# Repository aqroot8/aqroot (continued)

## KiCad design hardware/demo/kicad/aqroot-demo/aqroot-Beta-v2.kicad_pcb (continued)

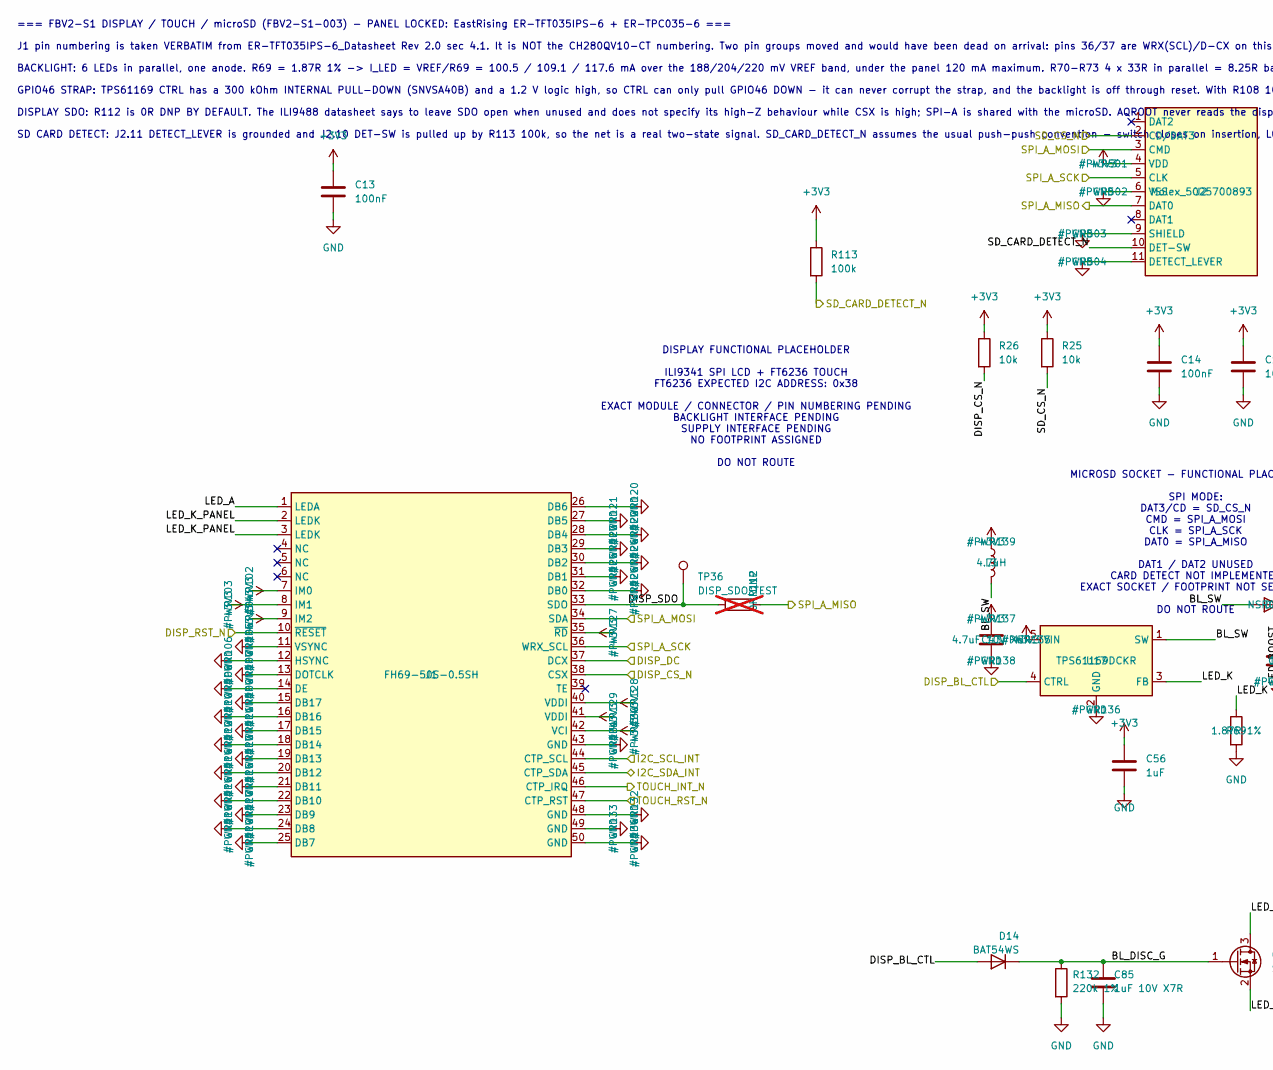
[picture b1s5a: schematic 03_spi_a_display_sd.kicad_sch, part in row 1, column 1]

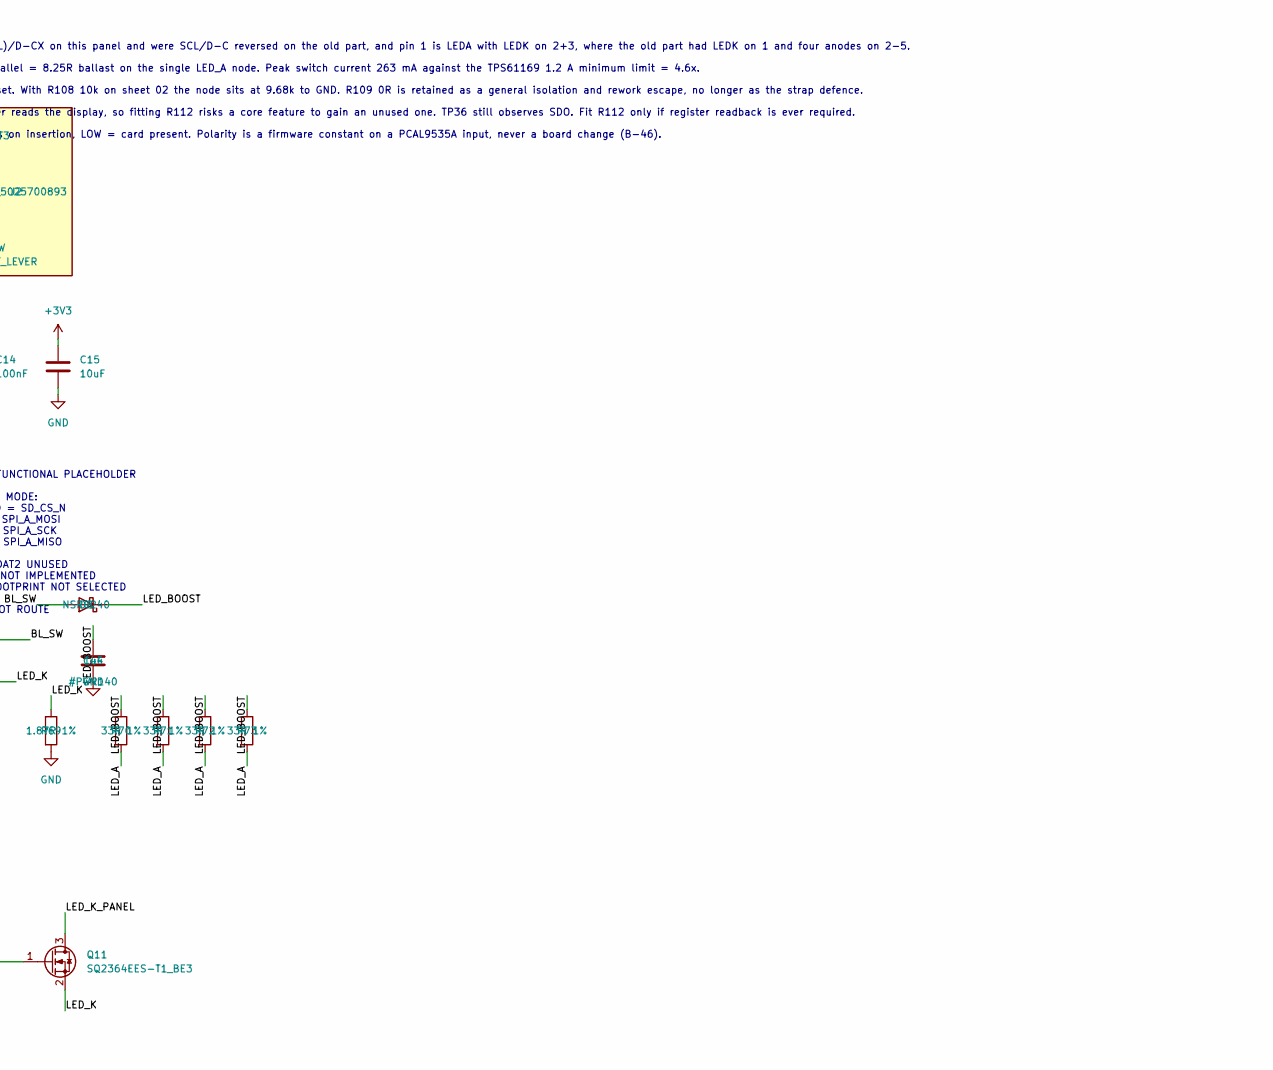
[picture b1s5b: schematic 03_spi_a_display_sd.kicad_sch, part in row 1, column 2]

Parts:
C13, C14: 100nF; C_0603_1608Metric; MPN CC0603KRX7R9BB104; LCSC C14663
C15: 10uF; C_0805_2012Metric; MPN GRM21BR61H106KE43L; LCSC C440198
C43: 4.7uF 10V X5R; C_0805_2012Metric; Voltage 16V; MPN CL21A475KAQNNNE; LCSC C1779
C44: 1uF; C_0805_2012Metric; Voltage 50V; MPN CL21B105KBFNNNE; LCSC C28323
C56: 1uF; C_0603_1608Metric; Voltage 16V; MPN CL10A105KB8NNNC; LCSC C15849
C85: 1uF 10V X7R; C_0603_1608Metric; MPN CC0603KRX7R8BB105; LCSC C106858
D8: NSR0240; D_SOD-323; MPN NSR0240HT1G; LCSC C152519
D14: BAT54WS; D_SOD-323; MPN BAT54WS-7-F; LCSC C124205
J1: FH69-50S-0.5SH; Hirose_FH69-50S-0.5SH; MPN FH69-50S-0.5SH; LCSC C25955556
J2: Molex_5025700893; MPN 5025700893; LCSC C429846
L3: 4.7uH; Coilcraft_XFL4020; MPN XFL4020-472MEC; LCSC C5156236
Q11: SQ2364EES-T1_BE3; SOT-23; MPN SQ2364EES-T1_BE3; LCSC C5758702
R25, R26: 10k; R_0603_1608Metric; MPN 0603WAF1002T5E; LCSC C25804
R69: 1.87R 1%; R_0603_1608Metric; Tolerance 1%; MPN 0603WAF187KT5E; LCSC C422967
R70, R71, R72, R73: 33R 1%; R_0603_1608Metric; Tolerance 1%; MPN 0603WAF330JT5E; LCSC C23140
R112: 0R DNP; R_0603_1608Metric; not fitted
R113: 100k; R_0603_1608Metric; MPN 0603WAF1003T5E; LCSC C25803
R132: 220k 1%; R_0603_1608Metric; MPN 0603WAF2203T5E; LCSC C22961
TP36: DISP_SDO_TEST; TestPoint_Pad_D1.0mm
U17: TPS61169DCKR; SOT-353_SC-70-5; MPN TPS61169DCKR; LCSC C71045

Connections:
+3V3: C13.1, C14.1, C15.1, C43.1, C56.1, J1.7 (IM0), J1.8 (IM1), J1.9 (IM2), J1.35 (~RD), J1.40 (VDDI), J1.41 (VDDI), J1.42 (VCI), J2.4 (VDD), L3.1, R25.1, R26.1, R113.1, U17.5 (VIN); also elsewhere on the board
/03_SPI_A_DISPLAY_SD/BL_DISC_G: C85.1, D14.1 (K), Q11.1 (G), R132.1
/03_SPI_A_DISPLAY_SD/BL_SW: D8.2 (A), L3.2, U17.1 (SW)
/03_SPI_A_DISPLAY_SD/DISP_SDO: J1.33 (SDO), R112.1, TP36.1
/03_SPI_A_DISPLAY_SD/LED_A: J1.1 (LEDA), R70.2, R71.2, R72.2, R73.2
/03_SPI_A_DISPLAY_SD/LED_BOOST: C44.1, D8.1 (K), R70.1, R71.1, R72.1, R73.1
/03_SPI_A_DISPLAY_SD/LED_K: Q11.2 (S), R69.1, U17.3 (FB)
/03_SPI_A_DISPLAY_SD/LED_K_PANEL: J1.2 (LEDK), J1.3 (LEDK), Q11.3 (D)
/DISP_BL_CTL: D14.2 (A), U17.4 (CTRL); also elsewhere on the board
/DISP_CS_N: J1.38 (CSX), R26.2; also elsewhere on the board
/DISP_DC: J1.37 (DCX); also elsewhere on the board
/DISP_RST_N: J1.10 (~RESET); also elsewhere on the board
/I2C_SCL_INT: J1.44 (CTP_SCL); also elsewhere on the board
/I2C_SDA_INT: J1.45 (CTP_SDA); also elsewhere on the board
/SD_CARD_DETECT_N: J2.10 (DET-SW), R113.2; also elsewhere on the board
/SD_CS_N: J2.2 (CD/DAT3), R25.2; also elsewhere on the board
/SPI_A_MISO: J2.7 (DAT0), R112.2; also elsewhere on the board
/SPI_A_MOSI: J1.34 (SDA), J2.3 (CMD); also elsewhere on the board
/SPI_A_SCK: J1.36 (WRX_SCL), J2.5 (CLK); also elsewhere on the board
/TOUCH_INT_N: J1.46 (CTP_IRQ); also elsewhere on the board
/TOUCH_RST_N: J1.47 (CTP_RST); also elsewhere on the board
GND: C13.2, C14.2, C15.2, C43.2, C44.2, C56.2, C85.2, J1.11 (VSYNC), J1.12 (HSYNC), J1.13 (DOTCLK), J1.14 (DE), J1.15 (DB17), J1.16 (DB16), J1.17 (DB15), J1.18 (DB14), J1.19 (DB13), J1.20 (DB12), J1.21 (DB11), J1.22 (DB10), J1.23 (DB9), J1.24 (DB8), J1.25 (DB7), J1.26 (DB6), J1.27 (DB5), J1.28 (DB4), J1.29 (DB3), J1.30 (DB2), J1.31 (DB1), J1.32 (DB0), J1.43 (GND), J1.48 (GND), J1.49 (GND), J1.50 (GND), J2.6 (VSS), J2.9 (SHIELD), J2.11 (DETECT_LEVER), R69.2, R132.2, U17.2 (GND); also elsewhere on the board

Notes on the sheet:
DISPLAY FUNCTIONAL PLACEHOLDER ILI9341 SPI LCD + FT6236 TOUCH FT6236 EXPECTED I2C ADDRESS: 0x38 EXACT MODULE / CONNECTOR / PIN NUMBERING PENDING BACKLIGHT INTERFACE PENDING SUPPLY INTERFACE PENDING NO FOOTPRINT ASSIGNED DO NOT ROUTE
MICROSD SOCKET - FUNCTIONAL PLACEHOLDER SPI MODE: DAT3/CD = SD_CS_N CMD = SPI_A_MOSI CLK = SPI_A_SCK DAT0 = SPI_A_MISO DAT1 / DAT2 UNUSED CARD DETECT NOT IMPLEMENTED EXACT SOCKET / FOOTPRINT NOT SELECTED DO NOT ROUTE
=== FBV2-S1 DISPLAY / TOUCH / microSD (FBV2-S1-003) - PANEL LOCKED: EastRising ER-TFT035IPS-6 + ER-TPC035-6 ===
J1 pin numbering is taken VERBATIM from ER-TFT035IPS-6_Datasheet Rev 2.0 sec 4.1. It is NOT the CH280QV10-CT numbering. Two pin groups moved and would have been dead on arrival: pins 36/37 are WRX(SCL)/D-CX on this panel and were SCL/D-C reversed on the old part, and pin 1 is LEDA with LEDK on 2+3,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
BACKLIGHT: 6 LEDs in parallel, one anode. R69 = 1.87R 1% -> I_LED = VREF/R69 = 100.5 / 109.1 / 117.6 mA over the 188/204/220 mV VREF band, under the panel 120 mA maximum. R70-R73 4 x 33R in parallel = 8.25R ballast on the single LED_A node. Peak switch current 263 mA against the TPS61169 1.2 A mini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
GPIO46 STRAP: TPS61169 CTRL has a 300 kOhm INTERNAL PULL-DOWN (SNVSA40B) and a 1.2 V logic high, so CTRL can only pull GPIO46 DOWN - it can never corrupt the strap, and the backlight is off through reset. With R108 10k on sheet 02 the node sits at 9.68k to GND. R109 0R is retained as a general isol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
DISPLAY SDO: R112 is 0R DNP BY DEFAULT. The ILI9488 datasheet says to leave SDO open when unused and does not specify its high-Z behaviour while CSX is high; SPI-A is shared with the microSD. AQROOT never reads the display, so fitting R112 risks a core feature to gain an unused one. TP36 still obse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
SD CARD DETECT: J2.11 DETECT_LEVER is grounded and J2.10 DET-SW is pulled up by R113 100k, so the net is a real two-state signal. SD_CARD_DETECT_N assumes the usual push-push convention - switch closes on insertion, LOW = card present. Polarity is a firmware constant on a PCAL9535A input, never a b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

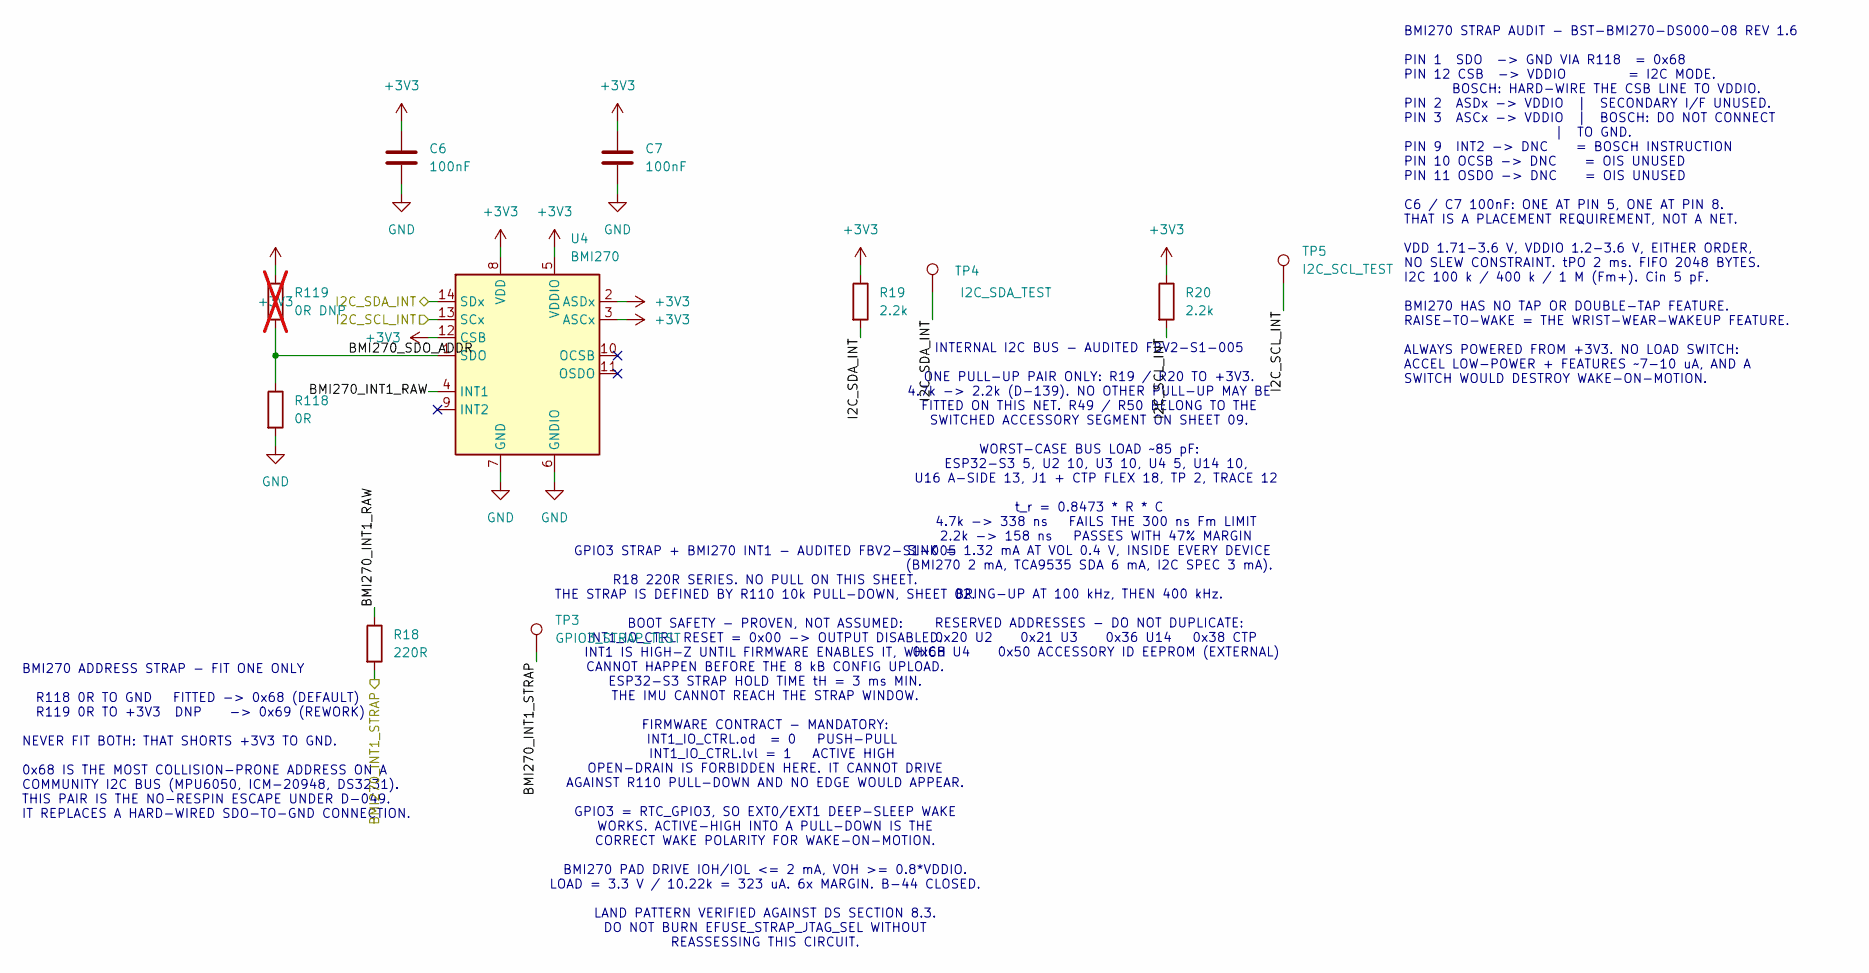
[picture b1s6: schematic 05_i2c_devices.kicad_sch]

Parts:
C6, C7: 100nF; C_0603_1608Metric; MPN CC0603KRX7R9BB104; LCSC C14663
R18: 220R; R_0603_1608Metric; MPN 0603WAF2200T5E; LCSC C22962
R19, R20: 2.2k; R_0603_1608Metric; MPN 0603WAF2201T5E; LCSC C4190
R118: 0R; R_0603_1608Metric; MPN 0603WAF0000T5E; LCSC C21189
R119: 0R DNP; R_0603_1608Metric; not fitted
TP3: GPIO3_STRAP_TEST; TestPoint_Pad_D1.0mm
TP4: I2C_SDA_TEST; TestPoint_Pad_D1.0mm
TP5: I2C_SCL_TEST; TestPoint_Pad_D1.0mm
U4: BMI270; Bosch_LGA-14_2.5x3.0mm_P0.5mm_BMI270; MPN BMI270; LCSC C2836813

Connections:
+3V3: C6.1, C7.1, R19.1, R20.1, R119.1, U4.2 (ASDx), U4.3 (ASCx), U4.5 (VDDIO), U4.8 (VDD), U4.12 (CSB); also elsewhere on the board
/05_I2C_DEVICES/BMI270_INT1_RAW: R18.1, U4.4 (INT1)
/05_I2C_DEVICES/BMI270_SDO_ADDR: R118.1, R119.2, U4.1 (SDO)
/BMI270_INT1_STRAP: R18.2, TP3.1; also elsewhere on the board
/I2C_SCL_INT: R20.2, TP5.1, U4.13 (SCx); also elsewhere on the board
/I2C_SDA_INT: R19.2, TP4.1, U4.14 (SDx); also elsewhere on the board
GND: C6.2, C7.2, R118.2, U4.6 (GNDIO), U4.7 (GND); also elsewhere on the board

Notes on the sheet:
GPIO3 STRAP + BMI270 INT1 - AUDITED FBV2-S1-005 R18 220R SERIES. NO PULL ON THIS SHEET. THE STRAP IS DEFINED BY R110 10k PULL-DOWN, SHEET 02. BOOT SAFETY - PROVEN, NOT ASSUMED: INT1_IO_CTRL RESET = 0x00 -> OUTPUT DISABLED. INT1 IS HIGH-Z UNTIL FIRMWARE ENABLES IT, WHICH CANNOT HAPPEN BEFORE THE 8 k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
INTERNAL I2C BUS - AUDITED FBV2-S1-005 ONE PULL-UP PAIR ONLY: R19 / R20 TO +3V3. 4.7k -> 2.2k (D-139). NO OTHER PULL-UP MAY BE FITTED ON THIS NET. R49 / R50 BELONG TO THE SWITCHED ACCESSORY SEGMENT ON SHEET 09. WORST-CASE BUS LOAD ~85 pF: ESP32-S3 5, U2 10, U3 10, U4 5, U14 10, U16 A-SIDE 13, J1 + 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
BMI270 ADDRESS STRAP - FIT ONE ONLY R118 0R TO GND FITTED -> 0x68 (DEFAULT) R119 0R TO +3V3 DNP -> 0x69 (REWORK) NEVER FIT BOTH: THAT SHORTS +3V3 TO GND. 0x68 IS THE MOST COLLISION-PRONE ADDRESS ON A COMMUNITY I2C BUS (MPU6050, ICM-20948, DS3231). THIS PAIR IS THE NO-RESPIN ESCAPE UNDER D-049. IT R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
BMI270 STRAP AUDIT - BST-BMI270-DS000-08 REV 1.6 PIN 1 SDO -> GND VIA R118 = 0x68 PIN 12 CSB -> VDDIO = I2C MODE. BOSCH: HARD-WIRE THE CSB LINE TO VDDIO. PIN 2 ASDx -> VDDIO | SECONDARY I/F UNUSED. PIN 3 ASCx -> VDDIO | BOSCH: DO NOT CONNECT | TO GND. PIN 9 INT2 -> DNC = BOSCH INSTRUCTION PIN 10 OC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

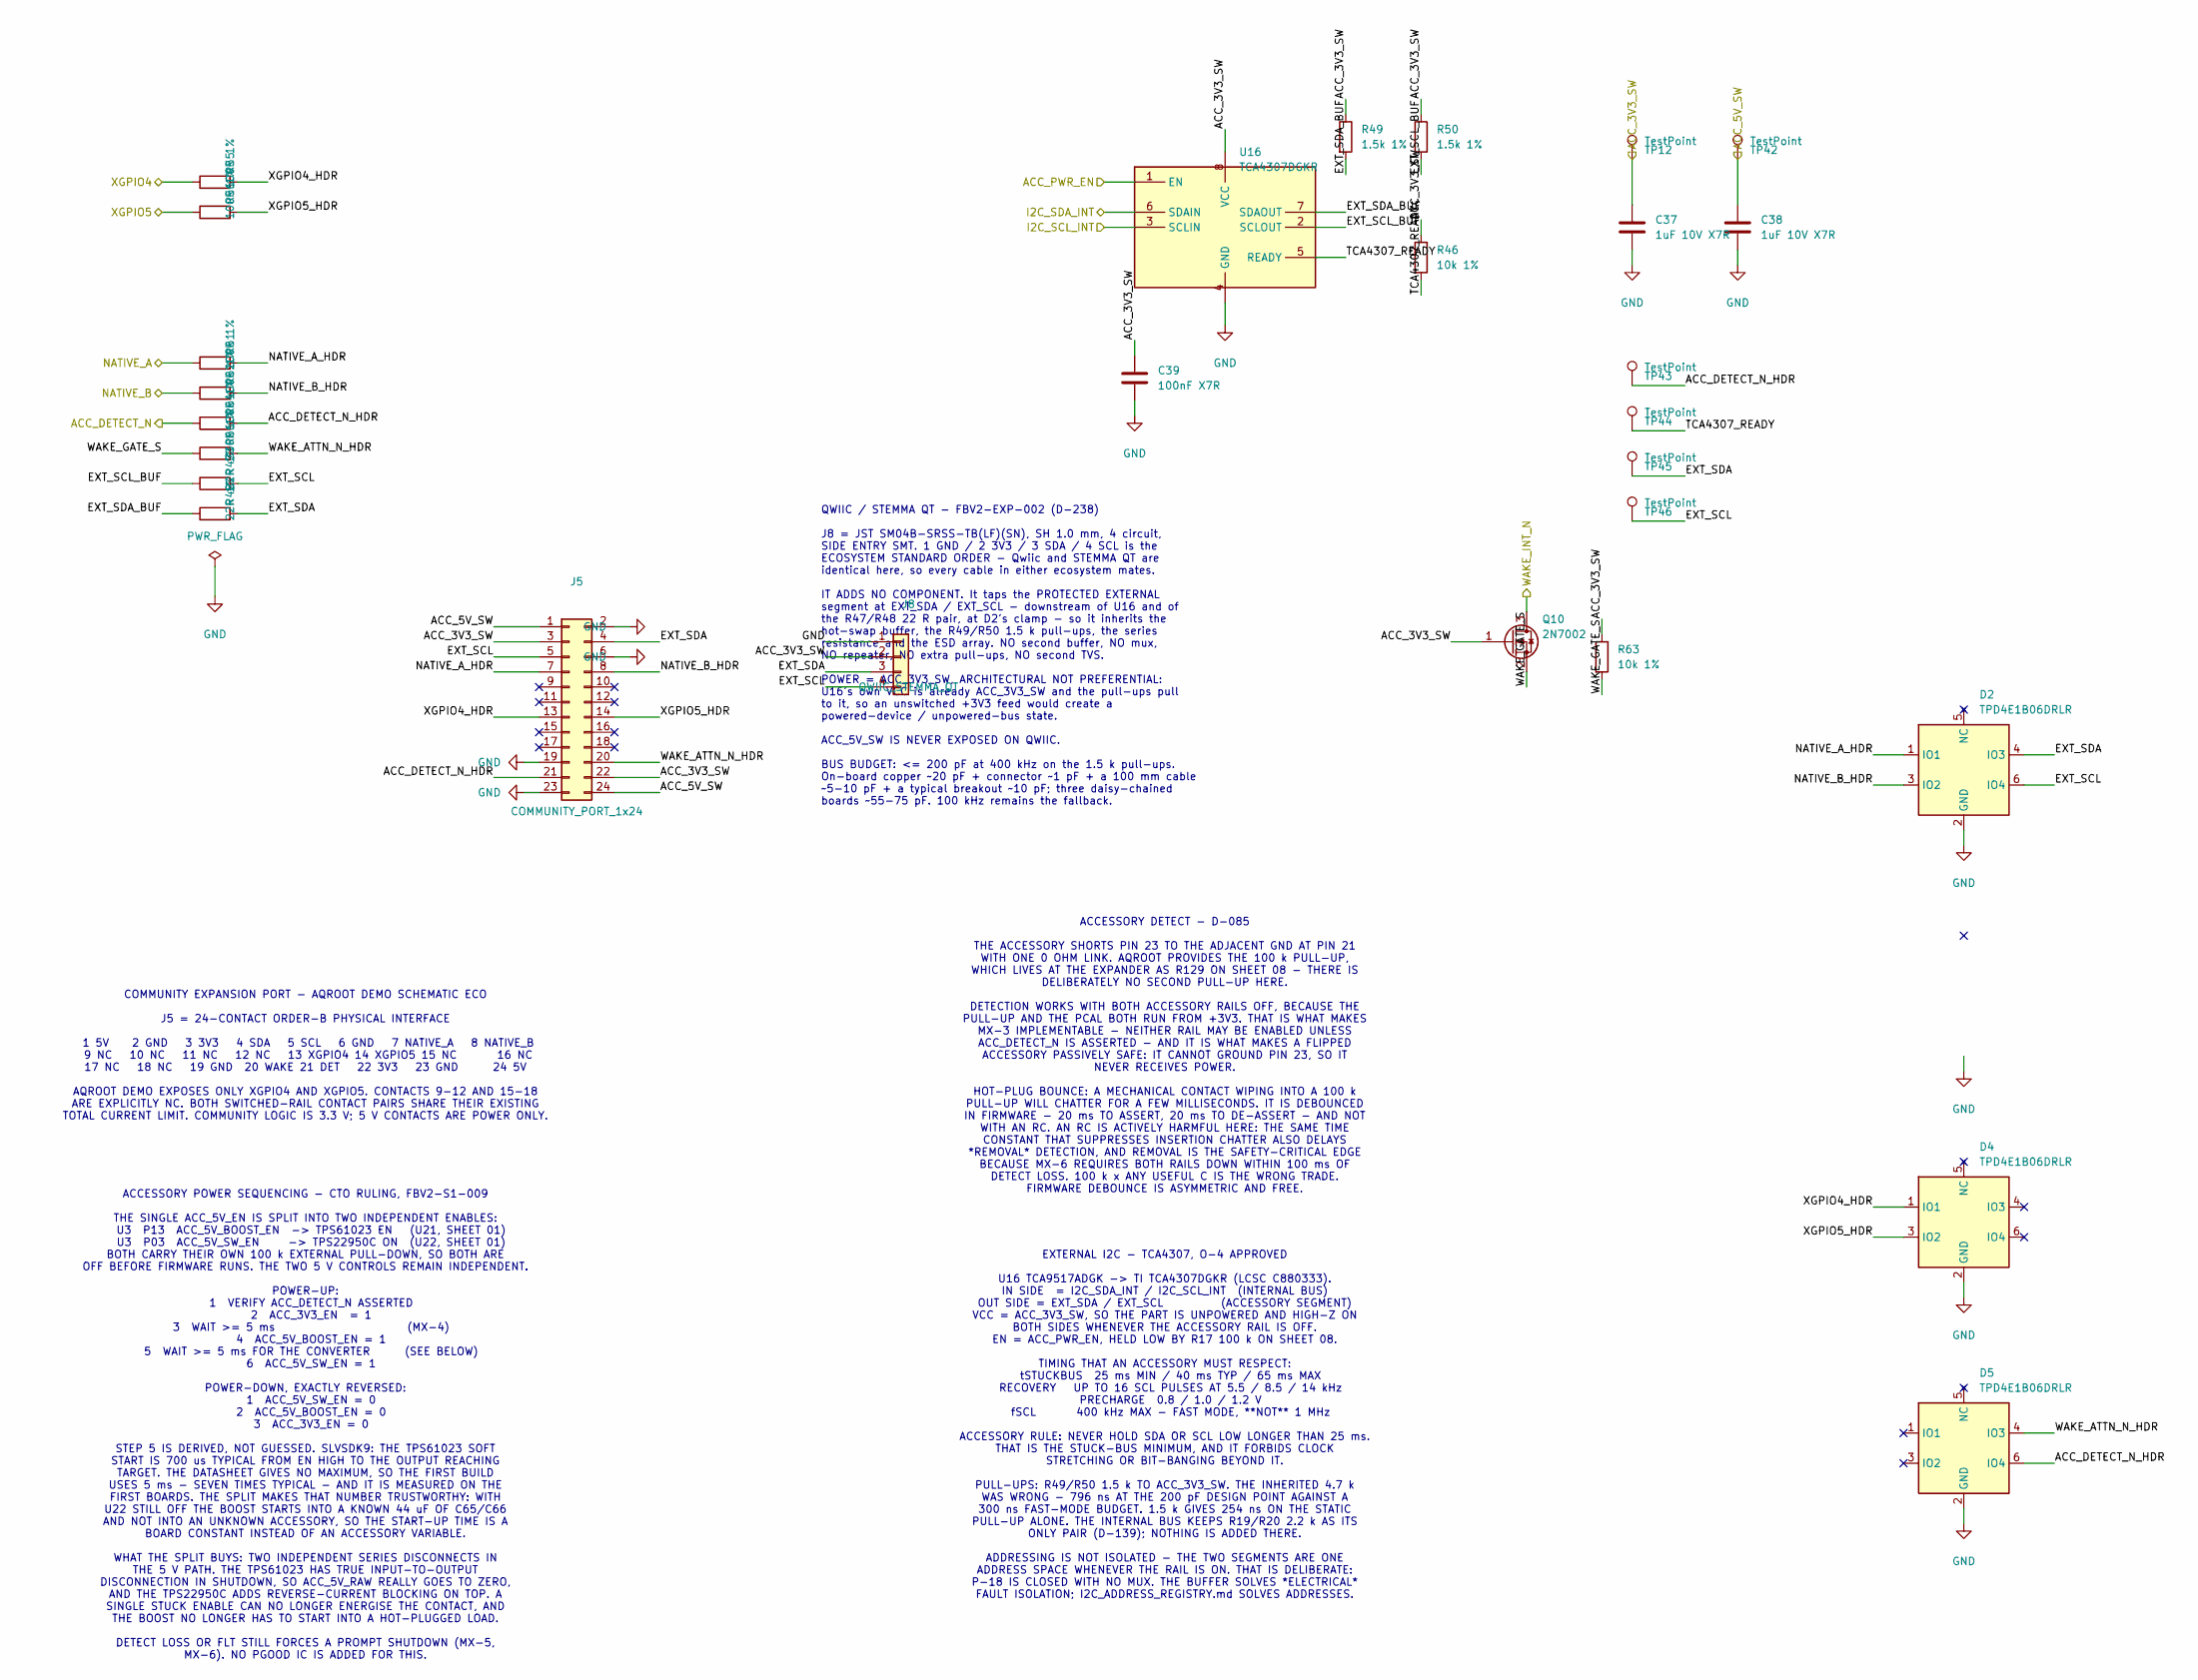
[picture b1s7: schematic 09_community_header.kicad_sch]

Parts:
C37, C38: 1uF 10V X7R; C_0603_1608Metric; MPN CC0603KRX7R8BB105; LCSC C106858
C39: 100nF X7R; C_0603_1608Metric; MPN CC0603KRX7R9BB104; LCSC C14663
D2, D4, D5: TPD4E1B06DRLR; SOT-563; MPN TPD4E1B06DRLR; LCSC C1972953
J5: COMMUNITY_PORT_1x24; Samtec_SSQ-124-02-G-S-RA; MPN SSQ-124-02-G-S-RA; LCSC C3323671
J8: QWIIC_STEMMA_QT; JST_SH_SM04B-SRSS-TB_1x04-1MP_P1.00mm_Horizontal; MPN SM04B-SRSS-TB(LF)(SN); LCSC C160404
Q10: 2N7002; SOT-23; MPN 2N7002; LCSC C8545
R46, R63: 10k 1%; R_0603_1608Metric; Tolerance 1%; MPN 0603WAF1002T5E; LCSC C25804
R47, R48: 22R 1%; R_0603_1608Metric; Tolerance 1%; MPN 0603WAF220JT5E; LCSC C23345
R49, R50: 1.5k 1%; R_0603_1608Metric; Tolerance 1%; MPN 0603WAF1501T5E; LCSC C22843
R55, R56, R61, R62, R64: 100R 1%; R_0603_1608Metric; Tolerance 1%; MPN 0603WAF1000T5E; LCSC C22775
R66: 330R 1%; R_0603_1608Metric; Tolerance 1%; MPN 0603WAF3300T5E; LCSC C23138
TP12, TP42, TP43, TP44, TP45, TP46: TestPoint; TestPoint_Pad_D1.0mm
U16: TCA4307DGKR; VSSOP-8_3x3mm_P0.65mm; MPN TCA4307DGKR; LCSC C880333

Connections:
/09_COMMUNITY_HEADER/ACC_DETECT_N_HDR: D5.6 (IO4), J5.21, R64.2, TP43.1
/09_COMMUNITY_HEADER/EXT_SCL: D2.6 (IO4), J5.5, J8.4, R47.2, TP46.1
/09_COMMUNITY_HEADER/EXT_SCL_BUF: R47.1, R50.2, U16.2 (SCLOUT)
/09_COMMUNITY_HEADER/EXT_SDA: D2.4 (IO3), J5.4, J8.3, R48.2, TP45.1
/09_COMMUNITY_HEADER/EXT_SDA_BUF: R48.1, R49.2, U16.7 (SDAOUT)
/09_COMMUNITY_HEADER/NATIVE_A_HDR: D2.1 (IO1), J5.7, R61.2
/09_COMMUNITY_HEADER/NATIVE_B_HDR: D2.3 (IO2), J5.8, R62.2
/09_COMMUNITY_HEADER/TCA4307_READY: R46.2, TP44.1, U16.5 (READY)
/09_COMMUNITY_HEADER/WAKE_ATTN_N_HDR: D5.4 (IO3), J5.20, R66.2
/09_COMMUNITY_HEADER/WAKE_GATE_S: Q10.2 (S), R63.2, R66.1
/09_COMMUNITY_HEADER/XGPIO4_HDR: D4.1 (IO1), J5.13, R55.2
/09_COMMUNITY_HEADER/XGPIO5_HDR: D4.3 (IO2), J5.14, R56.2
/ACC_3V3_SW: C37.1, C39.1, J5.3, J5.22, J8.2, Q10.1 (G), R46.1, R49.1, R50.1, R63.1, TP12.1, U16.8 (VCC); also elsewhere on the board
/ACC_5V_SW: C38.1, J5.1, J5.24, TP42.1; also elsewhere on the board
/ACC_DETECT_N: R64.1; also elsewhere on the board
/ACC_PWR_EN: U16.1 (EN); also elsewhere on the board
/I2C_SCL_INT: U16.3 (SCLIN); also elsewhere on the board
/I2C_SDA_INT: U16.6 (SDAIN); also elsewhere on the board
/NATIVE_A: R61.1; also elsewhere on the board
/NATIVE_B: R62.1; also elsewhere on the board
/WAKE_INT_N: Q10.3 (D); also elsewhere on the board
/XGPIO4: R55.1; also elsewhere on the board
/XGPIO5: R56.1; also elsewhere on the board
GND: C37.2, C38.2, C39.2, D2.2 (GND), D4.2 (GND), D5.2 (GND), J5.2, J5.6, J5.19, J5.23, J8.1, U16.4 (GND); also elsewhere on the board

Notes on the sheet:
COMMUNITY EXPANSION PORT - AQROOT DEMO SCHEMATIC ECO J5 = 24-CONTACT ORDER-B PHYSICAL INTERFACE 1 5V 2 GND 3 3V3 4 SDA 5 SCL 6 GND 7 NATIVE_A 8 NATIVE_B 9 NC 10 NC 11 NC 12 NC 13 XGPIO4 14 XGPIO5 15 NC 16 NC 17 NC 18 NC 19 GND 20 WAKE 21 DET 22 3V3 23 GND 24 5V AQROOT DEMO EXPOSES ONLY XGPIO4 AND X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
ACCESSORY DETECT - D-085 THE ACCESSORY SHORTS PIN 23 TO THE ADJACENT GND AT PIN 21 WITH ONE 0 OHM LINK. AQROOT PROVIDES THE 100 k PULL-UP, WHICH LIVES AT THE EXPANDER AS R129 ON SHEET 08 - THERE IS DELIBERATELY NO SECOND PULL-UP HERE. DETECTION WORKS WITH BOTH ACCESSORY RAILS OFF, BECAUSE THE PULL-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
ACCESSORY POWER SEQUENCING - CTO RULING, FBV2-S1-009 THE SINGLE ACC_5V_EN IS SPLIT INTO TWO INDEPENDENT ENABLES: U3 P13 ACC_5V_BOOST_EN -> TPS61023 EN (U21, SHEET 01) U3 P03 ACC_5V_SW_EN -> TPS22950C ON (U22, SHEET 01) BOTH CARRY THEIR OWN 100 k EXTERNAL PULL-DOWN, SO BOTH ARE OFF BEFORE FIRMWARE R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
EXTERNAL I2C - TCA4307, O-4 APPROVED U16 TCA9517ADGK -> TI TCA4307DGKR (LCSC C880333). IN SIDE = I2C_SDA_INT / I2C_SCL_INT (INTERNAL BUS) OUT SIDE = EXT_SDA / EXT_SCL (ACCESSORY SEGMENT) VCC = ACC_3V3_SW, SO THE PART IS UNPOWERED AND HIGH-Z ON BOTH SIDES WHENEVER THE ACCESSORY RAIL IS OFF. EN = ACC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
QWIIC / STEMMA QT - FBV2-EXP-002 (D-238) J8 = JST SM04B-SRSS-TB(LF)(SN), SH 1.0 mm, 4 circuit, SIDE ENTRY SMT. 1 GND / 2 3V3 / 3 SDA / 4 SCL is the ECOSYSTEM STANDARD ORDER - Qwiic and STEMMA QT are identical here, so every cable in either ecosystem mates. IT ADDS NO COMPONENT. It taps the PROTECTE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

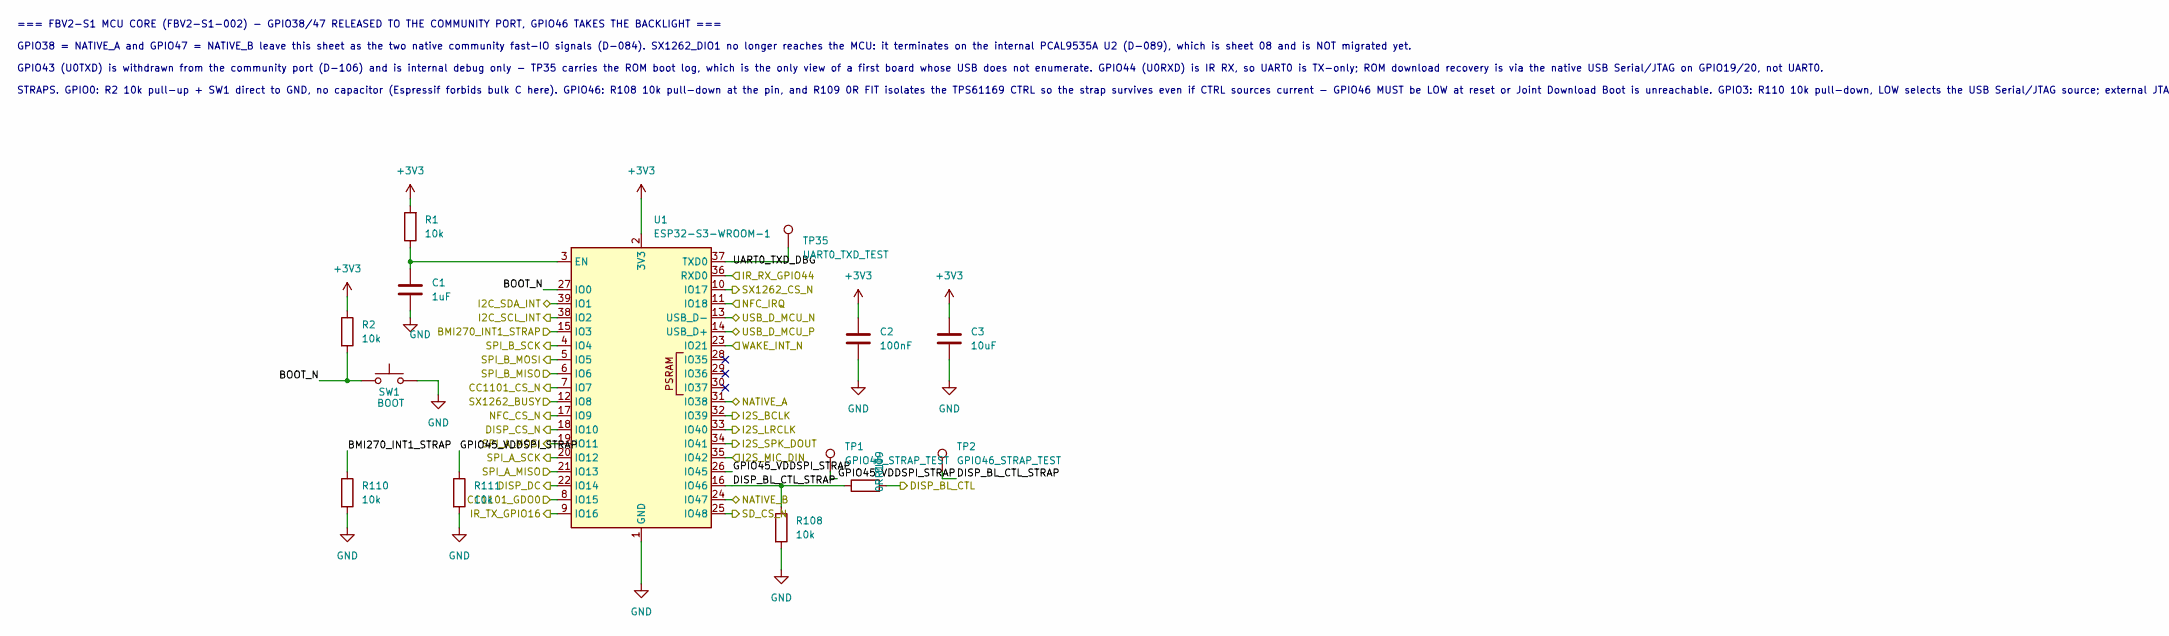
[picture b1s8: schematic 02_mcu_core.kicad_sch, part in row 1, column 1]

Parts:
C1: 1uF; C_0603_1608Metric; MPN CL10A105KB8NNNC; LCSC C15849
C2: 100nF; C_0603_1608Metric; MPN CC0603KRX7R9BB104; LCSC C14663
C3: 10uF; C_0805_2012Metric; MPN GRM21BR61H106KE43L; LCSC C440198
R1, R2, R108, R110, R111: 10k; R_0603_1608Metric; MPN 0603WAF1002T5E; LCSC C25804
R109: 0R FIT; R_0603_1608Metric; MPN 0603WAF0000T5E; LCSC C21189
SW1: BOOT; SW_SPST_PTS645Sx43SMTR92; MPN PTS645SM43SMTR92LFS; LCSC C221880
TP1: GPIO45_STRAP_TEST; TestPoint_Pad_D1.0mm
TP2: GPIO46_STRAP_TEST; TestPoint_Pad_D1.0mm
TP35: UART0_TXD_TEST; TestPoint_Pad_D1.0mm
U1: ESP32-S3-WROOM-1; MPN ESP32-S3-WROOM-1-N16R8; LCSC C2913202

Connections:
+3V3: C2.1, C3.1, R1.2, R2.1, U1.2 (3V3); also elsewhere on the board
/02_MCU_CORE/BOOT_N: R2.2, SW1.1, U1.27 (IO0)
/02_MCU_CORE/DISP_BL_CTL_STRAP: R108.1, R109.1, TP2.1, U1.16 (IO46)
/02_MCU_CORE/GPIO45_VDDSPI_STRAP: R111.1, TP1.1, U1.26 (IO45)
/02_MCU_CORE/UART0_TXD_DBG: TP35.1, U1.37 (TXD0)
/BMI270_INT1_STRAP: R110.1, U1.15 (IO3); also elsewhere on the board
/CC1101_CS_N: U1.7 (IO7); also elsewhere on the board
/CC1101_GDO0: U1.8 (IO15); also elsewhere on the board
/DISP_BL_CTL: R109.2; also elsewhere on the board
/DISP_CS_N: U1.18 (IO10); also elsewhere on the board
/DISP_DC: U1.22 (IO14); also elsewhere on the board
/I2C_SCL_INT: U1.38 (IO2); also elsewhere on the board
/I2C_SDA_INT: U1.39 (IO1); also elsewhere on the board
/I2S_BCLK: U1.32 (IO39); also elsewhere on the board
/I2S_LRCLK: U1.33 (IO40); also elsewhere on the board
/I2S_MIC_DIN: U1.35 (IO42); also elsewhere on the board
/I2S_SPK_DOUT: U1.34 (IO41); also elsewhere on the board
/IR_RX_GPIO44: U1.36 (RXD0); also elsewhere on the board
/IR_TX_GPIO16: U1.9 (IO16); also elsewhere on the board
/NATIVE_A: U1.31 (IO38); also elsewhere on the board
/NATIVE_B: U1.24 (IO47); also elsewhere on the board
/NFC_CS_N: U1.17 (IO9); also elsewhere on the board
/NFC_IRQ: U1.11 (IO18); also elsewhere on the board
/SD_CS_N: U1.25 (IO48); also elsewhere on the board
/SPI_A_MISO: U1.21 (IO13); also elsewhere on the board
/SPI_A_MOSI: U1.19 (IO11); also elsewhere on the board
/SPI_A_SCK: U1.20 (IO12); also elsewhere on the board
/SPI_B_MISO: U1.6 (IO6); also elsewhere on the board
/SPI_B_MOSI: U1.5 (IO5); also elsewhere on the board
/SPI_B_SCK: U1.4 (IO4); also elsewhere on the board
/SX1262_BUSY: U1.12 (IO8); also elsewhere on the board
/SX1262_CS_N: U1.10 (IO17); also elsewhere on the board
/USB_D_MCU_N: U1.13 (USB_D-); also elsewhere on the board
/USB_D_MCU_P: U1.14 (USB_D+); also elsewhere on the board
/WAKE_INT_N: U1.23 (IO21); also elsewhere on the board
GND: C1.1, C2.2, C3.2, R108.2, R110.2, R111.2, SW1.2, U1.1 (GND), U1.40 (GND), U1.41 (GND); also elsewhere on the board
unnamed: C1.2, R1.1, U1.3 (EN)

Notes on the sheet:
=== FBV2-S1 MCU CORE (FBV2-S1-002) - GPIO38/47 RELEASED TO THE COMMUNITY PORT, GPIO46 TAKES THE BACKLIGHT ===
GPIO38 = NATIVE_A and GPIO47 = NATIVE_B leave this sheet as the two native community fast-IO signals (D-084). SX1262_DIO1 no longer reaches the MCU: it terminates on the internal PCAL9535A U2 (D-089), which is sheet 08 and is NOT migrated yet.
GPIO43 (U0TXD) is withdrawn from the community port (D-106) and is internal debug only - TP35 carries the ROM boot log, which is the only view of a first board whose USB does not enumerate. GPIO44 (U0RXD) is IR RX, so UART0 is TX-only; ROM download recovery is via the native USB Serial/JTAG on GPIO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
STRAPS. GPIO0: R2 10k pull-up + SW1 direct to GND, no capacitor (Espressif forbids bulk C here). GPIO46: R108 10k pull-down at the pin, and R109 0R FIT isolates the TPS61169 CTRL so the strap survives even if CTRL sources current - GPIO46 MUST be LOW at reset or Joint Download Boot is unreachable. 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
